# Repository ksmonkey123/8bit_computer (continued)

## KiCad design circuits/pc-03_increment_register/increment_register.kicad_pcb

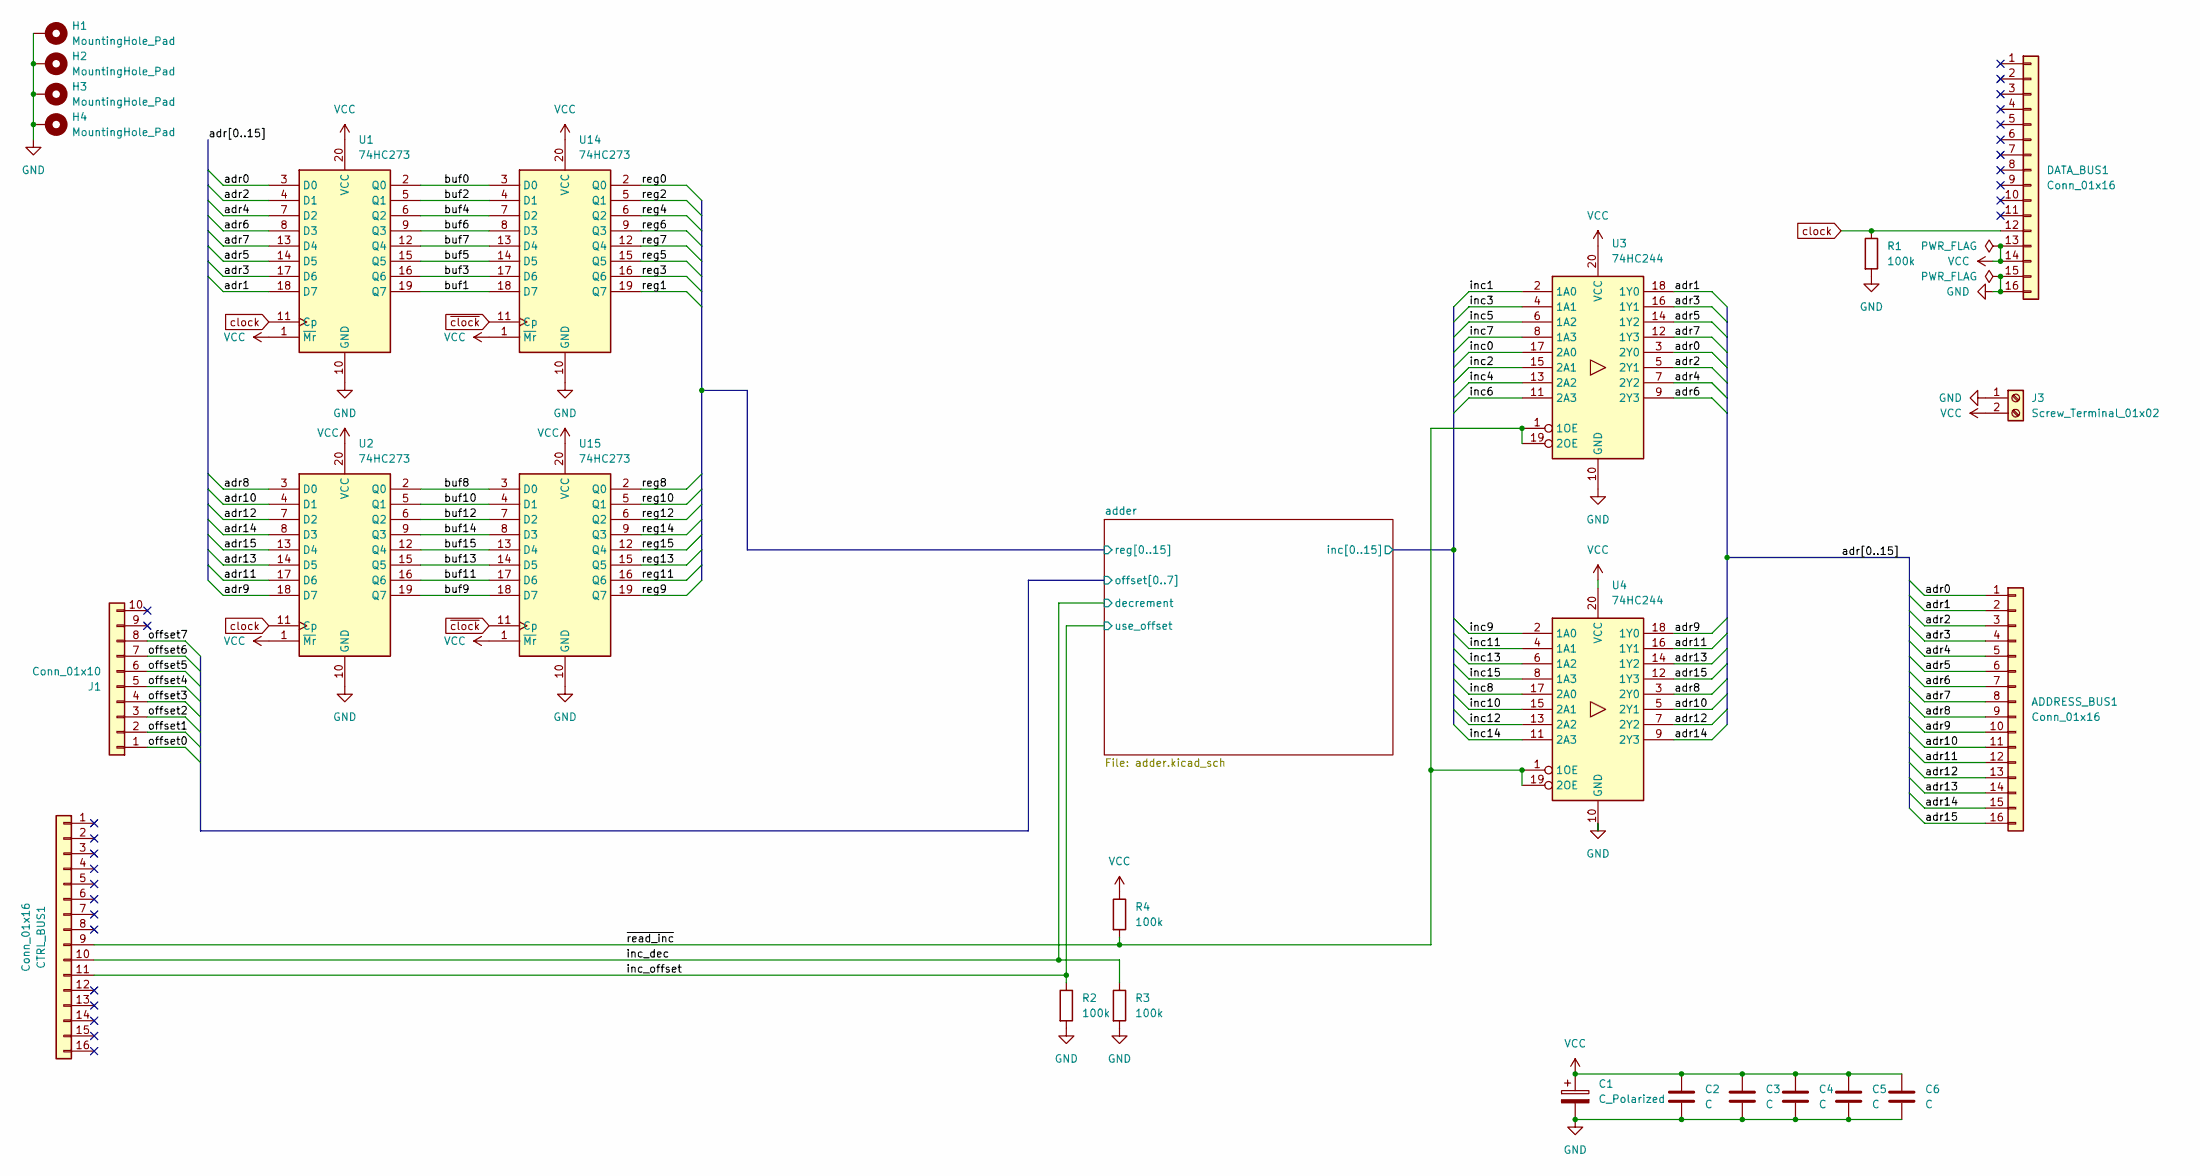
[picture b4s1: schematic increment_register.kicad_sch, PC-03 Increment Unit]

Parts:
ADDRESS_BUS1: Conn_01x16; IDC-Header_2x08_P2.54mm_Horizontal
C1: C_Polarized; CP_Elec_5x5.3
C2, C3, C4, C5, C6: C; C_0603_1608Metric
CTRL_BUS1: Conn_01x16; IDC-Header_2x08_P2.54mm_Horizontal
DATA_BUS1: Conn_01x16; IDC-Header_2x08_P2.54mm_Horizontal
H1, H2, H3, H4: MountingHole_Pad; MountingHole_3.2mm_M3_Pad_Via
J1: Conn_01x10; IDC-Header_2x05_P2.54mm_Horizontal
J3: Screw_Terminal_01x02; TerminalBlock_TE_282834-2_1x02_P2.54mm_Horizontal
R1, R2, R3, R4: 100k; R_0603_1608Metric
U1, U2, U14, U15: 74HC273; DIP-20_W7.62mm_LongPads
U3, U4: 74HC244; DIP-20_W7.62mm_LongPads

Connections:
/adder/inc0: U3.17 (2A0); also elsewhere on the board
/adder/inc1: U3.2 (1A0); also elsewhere on the board
/adder/inc2: U3.15 (2A1); also elsewhere on the board
/adder/inc3: U3.4 (1A1); also elsewhere on the board
/adder/inc4: U3.13 (2A2); also elsewhere on the board
/adder/inc5: U3.6 (1A2); also elsewhere on the board
/adder/inc6: U3.11 (2A3); also elsewhere on the board
/adder/inc7: U3.8 (1A3); also elsewhere on the board
/adder/inc8: U4.17 (2A0); also elsewhere on the board
/adder/inc9: U4.2 (1A0); also elsewhere on the board
/adder/inc10: U4.15 (2A1); also elsewhere on the board
/adder/inc11: U4.4 (1A1); also elsewhere on the board
/adder/inc12: U4.13 (2A2); also elsewhere on the board
/adder/inc13: U4.6 (1A2); also elsewhere on the board
/adder/inc14: U4.11 (2A3); also elsewhere on the board
/adder/inc15: U4.8 (1A3); also elsewhere on the board
/adder/offset0: J1.1; also elsewhere on the board
/adder/offset1: J1.2; also elsewhere on the board
/adder/offset2: J1.3; also elsewhere on the board
/adder/offset3: J1.4; also elsewhere on the board
/adder/offset4: J1.5; also elsewhere on the board
/adder/offset5: J1.6; also elsewhere on the board
/adder/offset6: J1.7; also elsewhere on the board
/adder/offset7: J1.8; also elsewhere on the board
/adder/reg0: U14.2 (Q0); also elsewhere on the board
/adder/reg1: U14.19 (Q7); also elsewhere on the board
/adder/reg2: U14.5 (Q1); also elsewhere on the board
/adder/reg3: U14.16 (Q6); also elsewhere on the board
/adder/reg4: U14.6 (Q2); also elsewhere on the board
/adder/reg5: U14.15 (Q5); also elsewhere on the board
/adder/reg6: U14.9 (Q3); also elsewhere on the board
/adder/reg7: U14.12 (Q4); also elsewhere on the board
/adder/reg8: U15.2 (Q0); also elsewhere on the board
/adder/reg9: U15.19 (Q7); also elsewhere on the board
/adder/reg10: U15.5 (Q1); also elsewhere on the board
/adder/reg11: U15.16 (Q6); also elsewhere on the board
/adder/reg12: U15.6 (Q2); also elsewhere on the board
/adder/reg13: U15.15 (Q5); also elsewhere on the board
/adder/reg14: U15.9 (Q3); also elsewhere on the board
/adder/reg15: U15.12 (Q4); also elsewhere on the board
/adr0: ADDRESS_BUS1.1, U1.3 (D0), U3.3 (2Y0)
/adr1: ADDRESS_BUS1.2, U1.18 (D7), U3.18 (1Y0)
/adr2: ADDRESS_BUS1.3, U1.4 (D1), U3.5 (2Y1)
/adr3: ADDRESS_BUS1.4, U1.17 (D6), U3.16 (1Y1)
/adr4: ADDRESS_BUS1.5, U1.7 (D2), U3.7 (2Y2)
/adr5: ADDRESS_BUS1.6, U1.14 (D5), U3.14 (1Y2)
/adr6: ADDRESS_BUS1.7, U1.8 (D3), U3.9 (2Y3)
/adr7: ADDRESS_BUS1.8, U1.13 (D4), U3.12 (1Y3)
/adr8: ADDRESS_BUS1.9, U2.3 (D0), U4.3 (2Y0)
/adr9: ADDRESS_BUS1.10, U2.18 (D7), U4.18 (1Y0)
/adr10: ADDRESS_BUS1.11, U2.4 (D1), U4.5 (2Y1)
/adr11: ADDRESS_BUS1.12, U2.17 (D6), U4.16 (1Y1)
/adr12: ADDRESS_BUS1.13, U2.7 (D2), U4.7 (2Y2)
/adr13: ADDRESS_BUS1.14, U2.14 (D5), U4.14 (1Y2)
/adr14: ADDRESS_BUS1.15, U2.8 (D3), U4.9 (2Y3)
/adr15: ADDRESS_BUS1.16, U2.13 (D4), U4.12 (1Y3)
/buf0: U1.2 (Q0), U14.3 (D0)
/buf1: U1.19 (Q7), U14.18 (D7)
/buf2: U1.5 (Q1), U14.4 (D1)
/buf3: U1.16 (Q6), U14.17 (D6)
/buf4: U1.6 (Q2), U14.7 (D2)
/buf5: U1.15 (Q5), U14.14 (D5)
/buf6: U1.9 (Q3), U14.8 (D3)
/buf7: U1.12 (Q4), U14.13 (D4)
/buf8: U2.2 (Q0), U15.3 (D0)
/buf9: U2.19 (Q7), U15.18 (D7)
/buf10: U2.5 (Q1), U15.4 (D1)
/buf11: U2.16 (Q6), U15.17 (D6)
/buf12: U2.6 (Q2), U15.7 (D2)
/buf13: U2.15 (Q5), U15.14 (D5)
/buf14: U2.9 (Q3), U15.8 (D3)
/buf15: U2.12 (Q4), U15.13 (D4)
/inc_dec: CTRL_BUS1.10, R3.1; also elsewhere on the board
/inc_offset: CTRL_BUS1.11, R2.1; also elsewhere on the board
/~read_inc: CTRL_BUS1.9, R4.2, U3.1 (1OE), U3.19 (2OE), U4.1 (1OE), U4.19 (2OE)
GND: C1.2, C2.2, C3.2, C4.2, C5.2, C6.2, DATA_BUS1.15, DATA_BUS1.16, H1.1, H2.1, H3.1, H4.1, J3.1, R1.2, R2.2, R3.2, U1.10 (GND), U2.10 (GND), U3.10 (GND), U4.10 (GND), U14.10 (GND), U15.10 (GND); also elsewhere on the board
VCC: C1.1, C2.1, C3.1, C4.1, C5.1, C6.1, DATA_BUS1.13, DATA_BUS1.14, J3.2, R4.1, U1.1 (~Mr), U1.20 (VCC), U2.1 (~Mr), U2.20 (VCC), U3.20 (VCC), U4.20 (VCC), U14.1 (~Mr), U14.20 (VCC), U15.1 (~Mr), U15.20 (VCC); also elsewhere on the board
clock: DATA_BUS1.12, R1.1, U1.11 (Cp), U2.11 (Cp); also elsewhere on the board
~clock: U14.11 (Cp), U15.11 (Cp); also elsewhere on the board

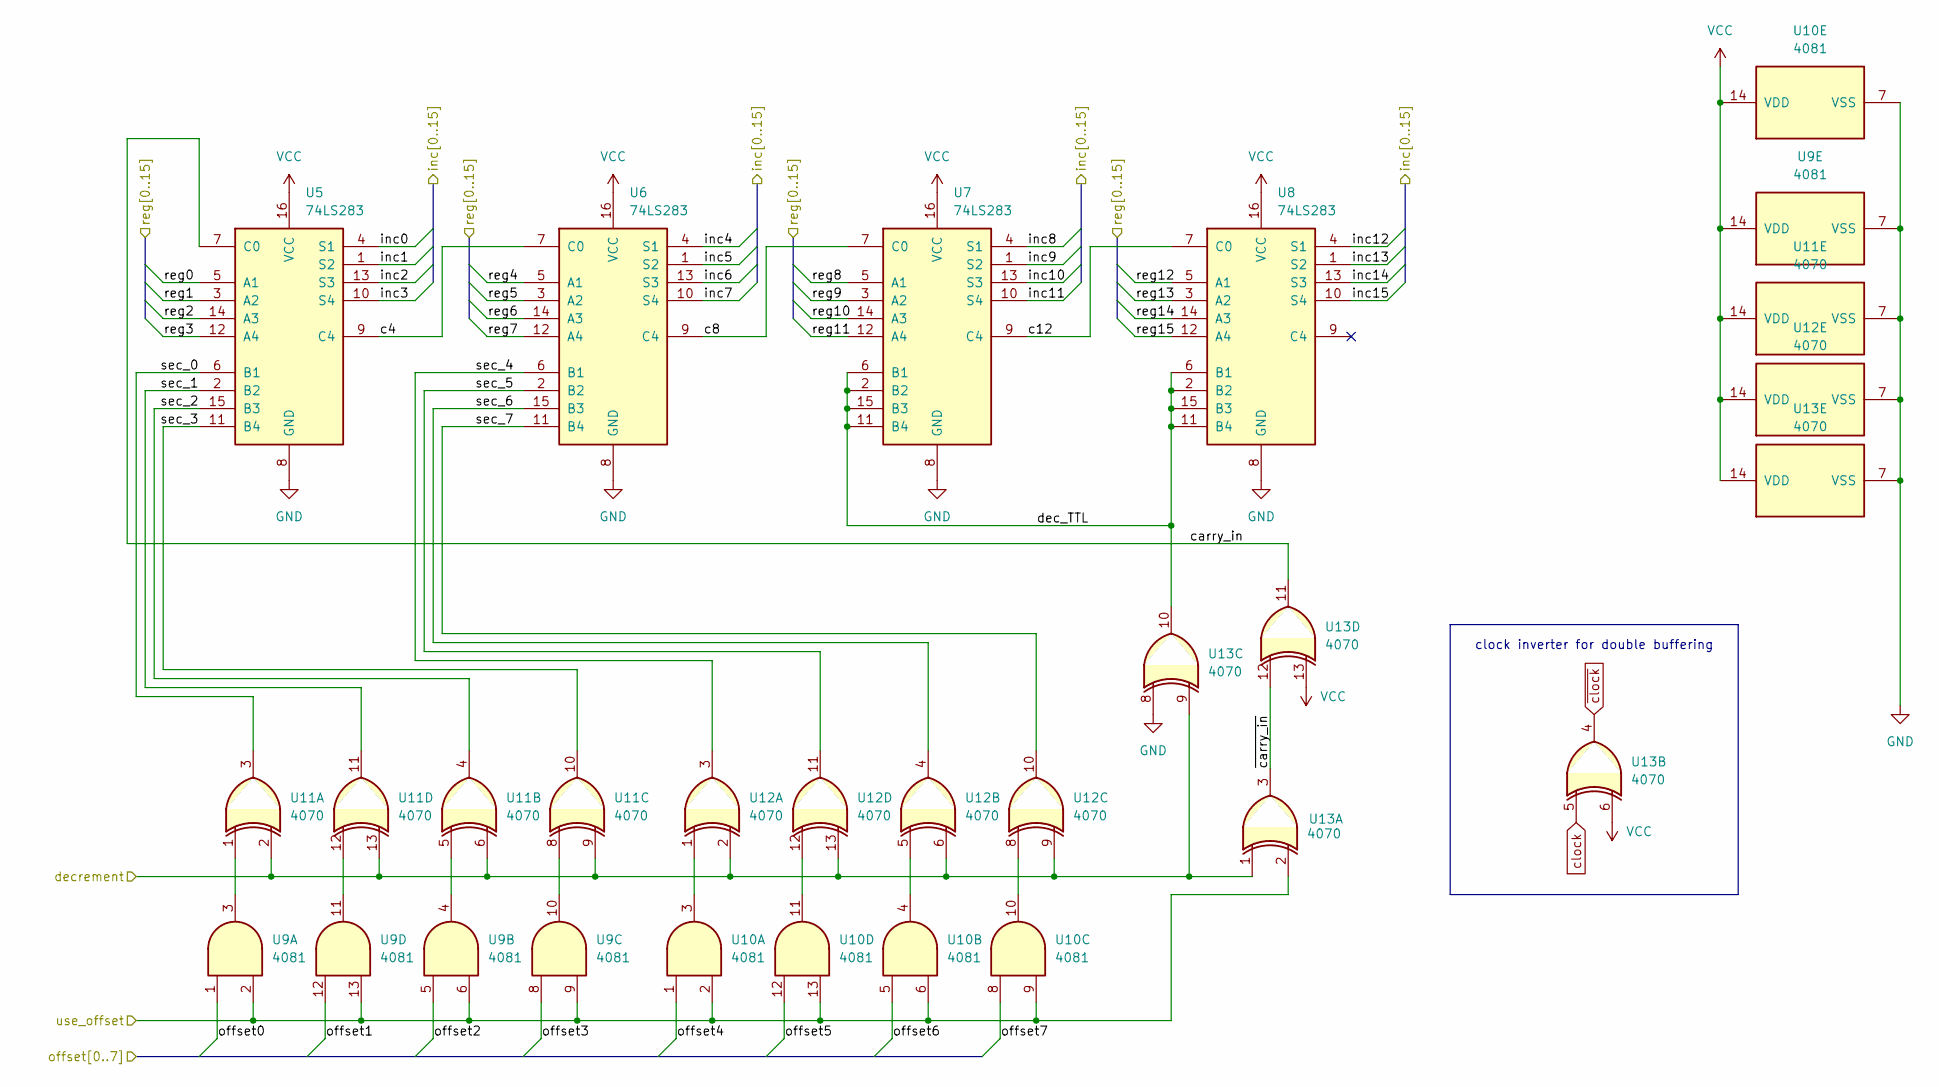
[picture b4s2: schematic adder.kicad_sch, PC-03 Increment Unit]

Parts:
U5, U6, U7, U8: 74LS283; DIP-16_W7.62mm_LongPads
U9, U10: 4081; DIP-14_W7.62mm_LongPads
U11, U12, U13: 4070; DIP-14_W7.62mm_LongPads

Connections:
/adder/c4: U5.9 (C4), U6.7 (C0)
/adder/c8: U6.9 (C4), U7.7 (C0)
/adder/c12: U7.9 (C4), U8.7 (C0)
/adder/carry_in: U5.7 (C0), U13.11
/adder/dec_TTL: U7.2 (B2), U7.6 (B1), U7.11 (B4), U7.15 (B3), U8.2 (B2), U8.6 (B1), U8.11 (B4), U8.15 (B3), U13.10
/adder/inc0: U5.4 (S1); also elsewhere on the board
/adder/inc1: U5.1 (S2); also elsewhere on the board
/adder/inc2: U5.13 (S3); also elsewhere on the board
/adder/inc3: U5.10 (S4); also elsewhere on the board
/adder/inc4: U6.4 (S1); also elsewhere on the board
/adder/inc5: U6.1 (S2); also elsewhere on the board
/adder/inc6: U6.13 (S3); also elsewhere on the board
/adder/inc7: U6.10 (S4); also elsewhere on the board
/adder/inc8: U7.4 (S1); also elsewhere on the board
/adder/inc9: U7.1 (S2); also elsewhere on the board
/adder/inc10: U7.13 (S3); also elsewhere on the board
/adder/inc11: U7.10 (S4); also elsewhere on the board
/adder/inc12: U8.4 (S1); also elsewhere on the board
/adder/inc13: U8.1 (S2); also elsewhere on the board
/adder/inc14: U8.13 (S3); also elsewhere on the board
/adder/inc15: U8.10 (S4); also elsewhere on the board
/adder/offset0: U9.1; also elsewhere on the board
/adder/offset1: U9.12; also elsewhere on the board
/adder/offset2: U9.5; also elsewhere on the board
/adder/offset3: U9.8; also elsewhere on the board
/adder/offset4: U10.1; also elsewhere on the board
/adder/offset5: U10.12; also elsewhere on the board
/adder/offset6: U10.5; also elsewhere on the board
/adder/offset7: U10.8; also elsewhere on the board
/adder/reg0: U5.5 (A1); also elsewhere on the board
/adder/reg1: U5.3 (A2); also elsewhere on the board
/adder/reg2: U5.14 (A3); also elsewhere on the board
/adder/reg3: U5.12 (A4); also elsewhere on the board
/adder/reg4: U6.5 (A1); also elsewhere on the board
/adder/reg5: U6.3 (A2); also elsewhere on the board
/adder/reg6: U6.14 (A3); also elsewhere on the board
/adder/reg7: U6.12 (A4); also elsewhere on the board
/adder/reg8: U7.5 (A1); also elsewhere on the board
/adder/reg9: U7.3 (A2); also elsewhere on the board
/adder/reg10: U7.14 (A3); also elsewhere on the board
/adder/reg11: U7.12 (A4); also elsewhere on the board
/adder/reg12: U8.5 (A1); also elsewhere on the board
/adder/reg13: U8.3 (A2); also elsewhere on the board
/adder/reg14: U8.14 (A3); also elsewhere on the board
/adder/reg15: U8.12 (A4); also elsewhere on the board
/adder/sec_0: U5.6 (B1), U11.3
/adder/sec_1: U5.2 (B2), U11.11
/adder/sec_2: U5.15 (B3), U11.4
/adder/sec_3: U5.11 (B4), U11.10
/adder/sec_4: U6.6 (B1), U12.3
/adder/sec_5: U6.2 (B2), U12.11
/adder/sec_6: U6.15 (B3), U12.4
/adder/sec_7: U6.11 (B4), U12.10
/adder/~carry_in: U13.3, U13.12
/inc_dec: U11.2, U11.6, U11.9, U11.13, U12.2, U12.6, U12.9, U12.13, U13.1, U13.9; also elsewhere on the board
/inc_offset: U9.2, U9.6, U9.9, U9.13, U10.2, U10.6, U10.9, U10.13, U13.2; also elsewhere on the board
GND: U5.8 (GND), U6.8 (GND), U7.8 (GND), U8.8 (GND), U9.7 (VSS), U10.7 (VSS), U11.7 (VSS), U12.7 (VSS), U13.7 (VSS), U13.8; also elsewhere on the board
unnamed: U10.3, U12.1
unnamed: U10.4, U12.5
unnamed: U10.10, U12.8
unnamed: U10.11, U12.12
unnamed: U9.3, U11.1
unnamed: U9.4, U11.5
unnamed: U9.10, U11.8
unnamed: U9.11, U11.12
VCC: U5.16 (VCC), U6.16 (VCC), U7.16 (VCC), U8.16 (VCC), U9.14 (VDD), U10.14 (VDD), U11.14 (VDD), U12.14 (VDD), U13.6, U13.13, U13.14 (VDD); also elsewhere on the board
clock: U13.5; also elsewhere on the board
~clock: U13.4; also elsewhere on the board

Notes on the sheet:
clock inverter for double buffering

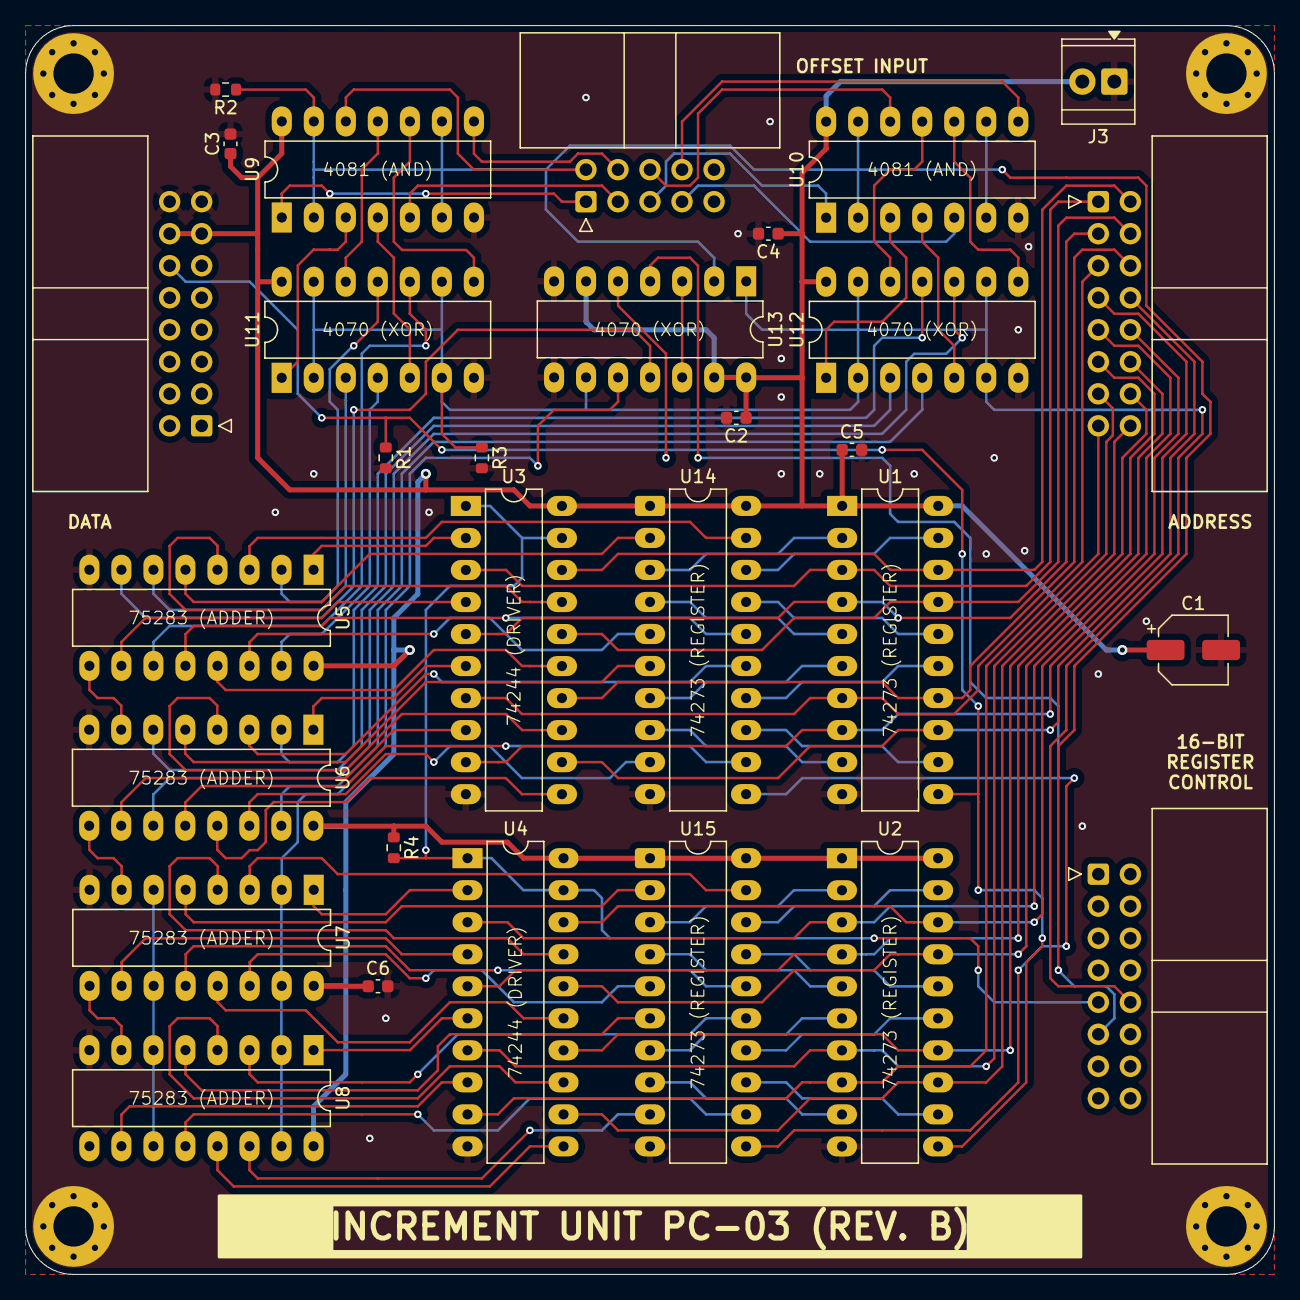
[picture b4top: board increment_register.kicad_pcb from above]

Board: 2 copper layers, 99.1 x 99.1 mm, 34 parts (0 on the bottom side), 101 nets.

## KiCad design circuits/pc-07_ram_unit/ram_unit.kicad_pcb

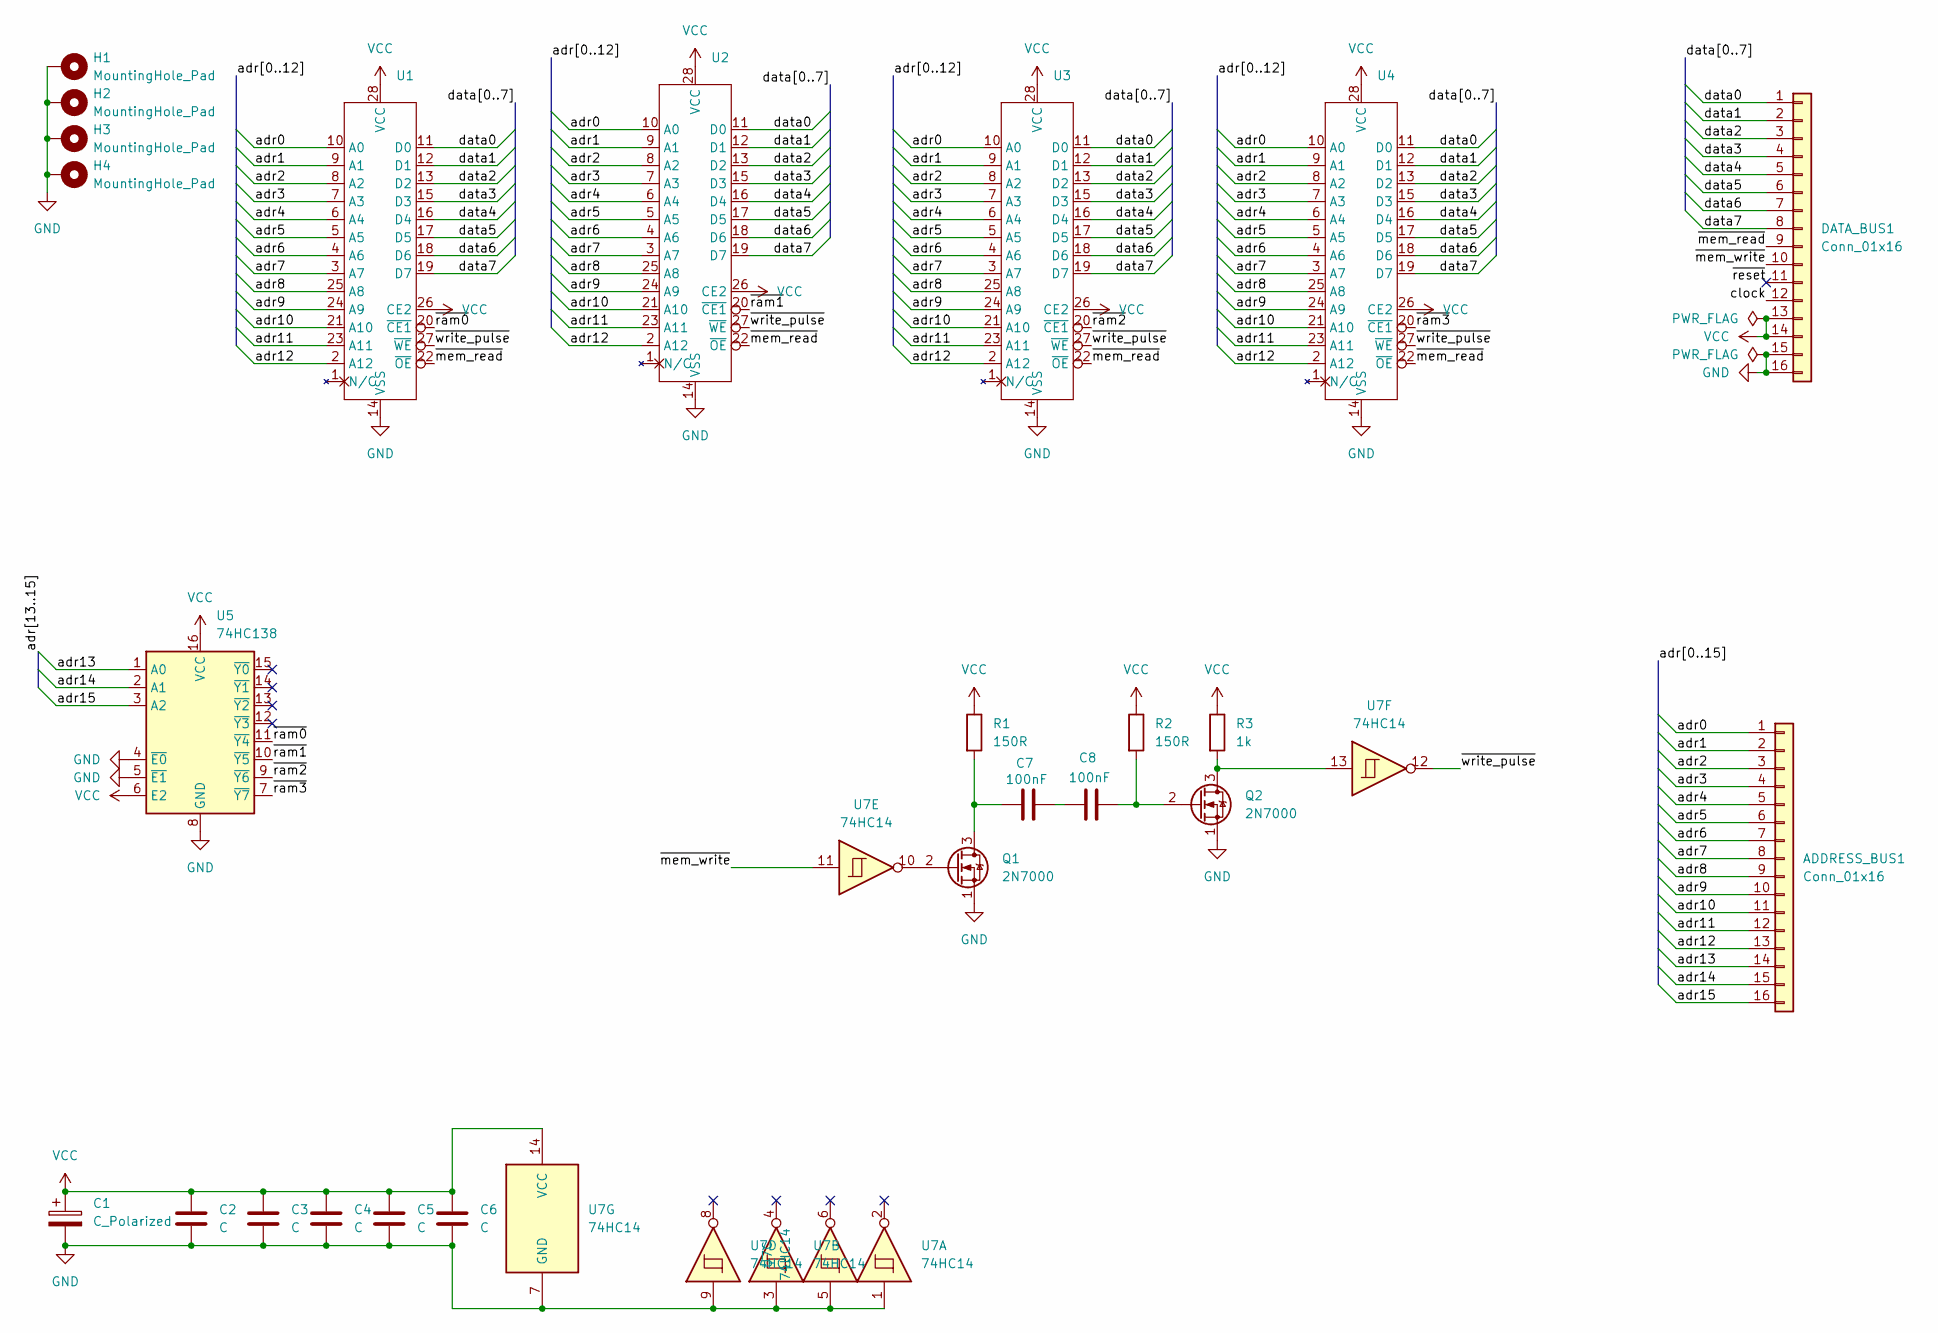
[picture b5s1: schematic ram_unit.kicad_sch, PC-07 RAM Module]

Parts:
ADDRESS_BUS1: Conn_01x16; IDC-Header_2x08_P2.54mm_Horizontal
C1: C_Polarized; CP_Elec_5x5.3
C2, C3, C4, C5, C6: C; C_0603_1608Metric
C7, C8: 100nF; C_0603_1608Metric
DATA_BUS1: Conn_01x16; IDC-Header_2x08_P2.54mm_Horizontal
H1, H2, H3, H4: MountingHole_Pad; MountingHole_3.2mm_M3_Pad_Via
Q1, Q2: 2N7000; TO-92_Inline_Wide
R1, R2: 150R; R_0603_1608Metric
R3: 1k; R_0603_1608Metric
U1, U2, U3, U4: DIP-28_W7.62mm_LongPads
U5: 74HC138; DIP-16_W7.62mm_LongPads
U7: 74HC14; DIP-14_W7.62mm

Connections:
/adr0: ADDRESS_BUS1.1, U1.10 (A0), U2.10 (A0), U3.10 (A0), U4.10 (A0)
/adr1: ADDRESS_BUS1.2, U1.9 (A1), U2.9 (A1), U3.9 (A1), U4.9 (A1)
/adr2: ADDRESS_BUS1.3, U1.8 (A2), U2.8 (A2), U3.8 (A2), U4.8 (A2)
/adr3: ADDRESS_BUS1.4, U1.7 (A3), U2.7 (A3), U3.7 (A3), U4.7 (A3)
/adr4: ADDRESS_BUS1.5, U1.6 (A4), U2.6 (A4), U3.6 (A4), U4.6 (A4)
/adr5: ADDRESS_BUS1.6, U1.5 (A5), U2.5 (A5), U3.5 (A5), U4.5 (A5)
/adr6: ADDRESS_BUS1.7, U1.4 (A6), U2.4 (A6), U3.4 (A6), U4.4 (A6)
/adr7: ADDRESS_BUS1.8, U1.3 (A7), U2.3 (A7), U3.3 (A7), U4.3 (A7)
/adr8: ADDRESS_BUS1.9, U1.25 (A8), U2.25 (A8), U3.25 (A8), U4.25 (A8)
/adr9: ADDRESS_BUS1.10, U1.24 (A9), U2.24 (A9), U3.24 (A9), U4.24 (A9)
/adr10: ADDRESS_BUS1.11, U1.21 (A10), U2.21 (A10), U3.21 (A10), U4.21 (A10)
/adr11: ADDRESS_BUS1.12, U1.23 (A11), U2.23 (A11), U3.23 (A11), U4.23 (A11)
/adr12: ADDRESS_BUS1.13, U1.2 (A12), U2.2 (A12), U3.2 (A12), U4.2 (A12)
/adr13: ADDRESS_BUS1.14, U5.1 (A0)
/adr14: ADDRESS_BUS1.15, U5.2 (A1)
/adr15: ADDRESS_BUS1.16, U5.3 (A2)
/clock: DATA_BUS1.12
/data0: DATA_BUS1.1, U1.11 (D0), U2.11 (D0), U3.11 (D0), U4.11 (D0)
/data1: DATA_BUS1.2, U1.12 (D1), U2.12 (D1), U3.12 (D1), U4.12 (D1)
/data2: DATA_BUS1.3, U1.13 (D2), U2.13 (D2), U3.13 (D2), U4.13 (D2)
/data3: DATA_BUS1.4, U1.15 (D3), U2.15 (D3), U3.15 (D3), U4.15 (D3)
/data4: DATA_BUS1.5, U1.16 (D4), U2.16 (D4), U3.16 (D4), U4.16 (D4)
/data5: DATA_BUS1.6, U1.17 (D5), U2.17 (D5), U3.17 (D5), U4.17 (D5)
/data6: DATA_BUS1.7, U1.18 (D6), U2.18 (D6), U3.18 (D6), U4.18 (D6)
/data7: DATA_BUS1.8, U1.19 (D7), U2.19 (D7), U3.19 (D7), U4.19 (D7)
/~mem_read: DATA_BUS1.9, U1.22 (~OE), U2.22 (~OE), U3.22 (~OE), U4.22 (~OE)
/~mem_write: DATA_BUS1.10, U7.11
/~ram0: U1.20 (~CE1), U5.11 (~Y4)
/~ram1: U2.20 (~CE1), U5.10 (~Y5)
/~ram2: U3.20 (~CE1), U5.9 (~Y6)
/~ram3: U4.20 (~CE1), U5.7 (~Y7)
/~reset: DATA_BUS1.11
/~write_pulse: U1.27 (~WE), U2.27 (~WE), U3.27 (~WE), U4.27 (~WE), U7.12
GND: C1.2, C2.2, C3.2, C4.2, C5.2, C6.2, DATA_BUS1.15, DATA_BUS1.16, H1.1, H2.1, H3.1, H4.1, Q1.1 (S), Q2.1 (S), U1.14 (VSS), U2.14 (VSS), U3.14 (VSS), U4.14 (VSS), U5.4 (~E0), U5.5 (~E1), U5.8 (GND), U7.1, U7.3, U7.5, U7.7 (GND), U7.9
unnamed: C7.2, C8.1
unnamed: C7.1, Q1.3 (D), R1.2
unnamed: Q1.2 (G), U7.10
unnamed: Q2.3 (D), R3.2, U7.13
unnamed: C8.2, Q2.2 (G), R2.2
VCC: C1.1, C2.1, C3.1, C4.1, C5.1, C6.1, DATA_BUS1.13, DATA_BUS1.14, R1.1, R2.1, R3.1, U1.26 (CE2), U1.28 (VCC), U2.26 (CE2), U2.28 (VCC), U3.26 (CE2), U3.28 (VCC), U4.26 (CE2), U4.28 (VCC), U5.6 (E2), U5.16 (VCC), U7.14 (VCC)

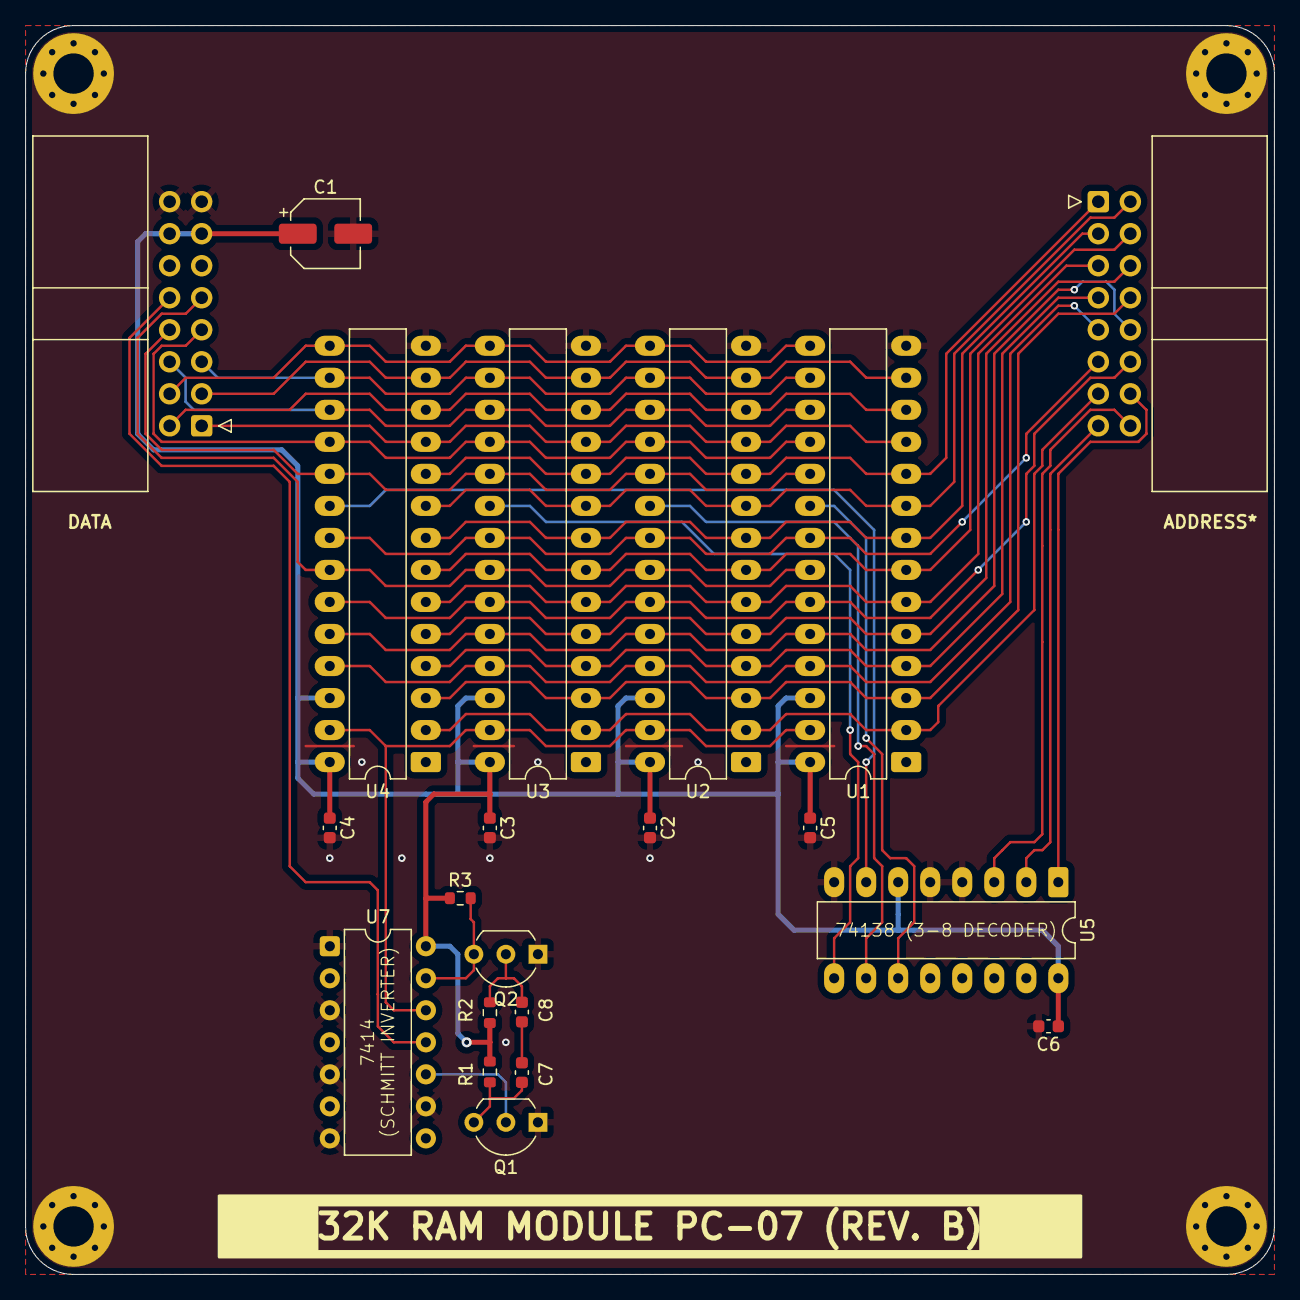
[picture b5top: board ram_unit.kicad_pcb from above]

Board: 2 copper layers, 99.1 x 99.1 mm, 25 parts (0 on the bottom side), 38 nets.
